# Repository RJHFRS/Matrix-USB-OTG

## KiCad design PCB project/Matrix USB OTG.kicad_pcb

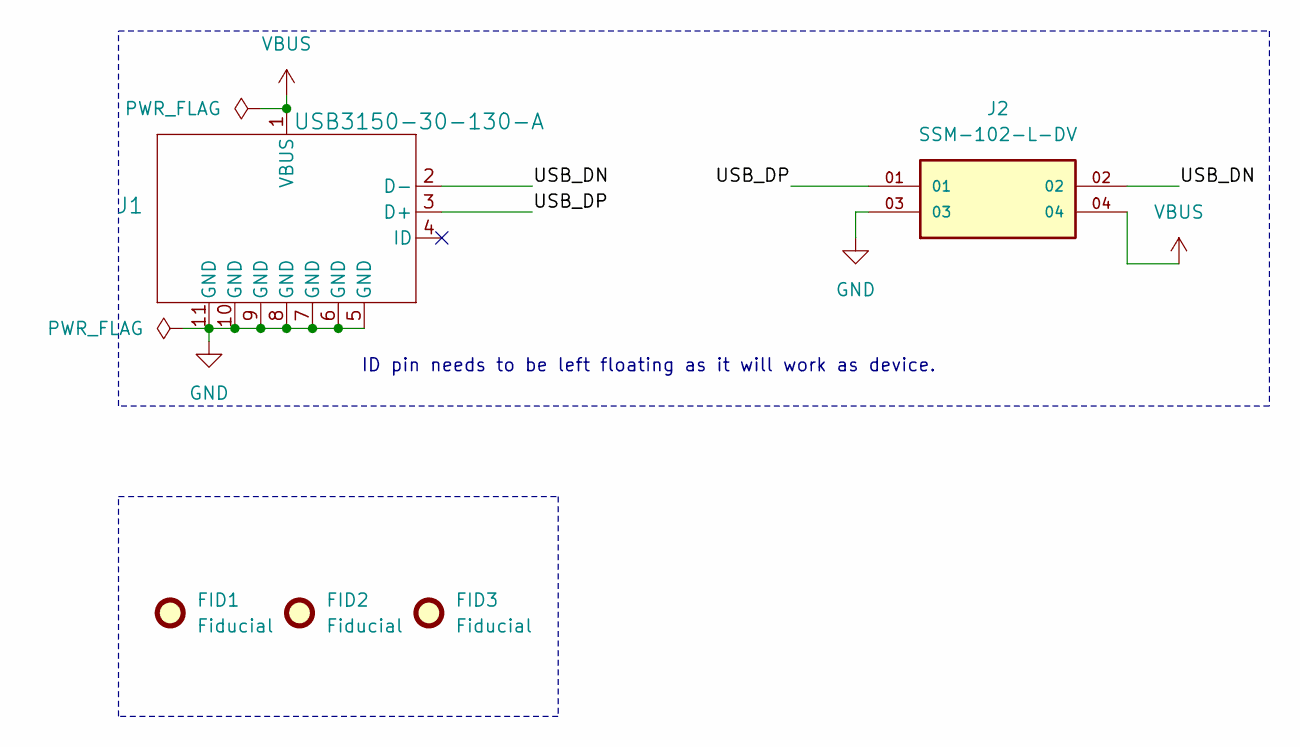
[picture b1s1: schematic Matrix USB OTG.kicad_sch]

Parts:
FID1, FID2, FID3: Fiducial; Fiducial_0.5mm_Mask1.5mm
J1: USB3150-30-130-A; USB3150-30-130-A_GCC; Digikey PN 2073-USB3150-30-130-ACT-ND - Cut Tape (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
J2: SSM-102-L-DV; SAMTEC_SSM-102-L-DV; PARTREV R; Digikey PN 612-SSM-102-L-DV-ND

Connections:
/USB_DN: J1.2 (D-), J2.02
/USB_DP: J1.3 (D+), J2.01
GND: J1.5 (GND), J1.6 (GND), J1.7 (GND), J1.8 (GND), J1.9 (GND), J1.10 (GND), J1.11 (GND), J2.03
VBUS: J1.1 (VBUS), J2.04

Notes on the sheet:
ID pin needs to be left floating as it will work as device.

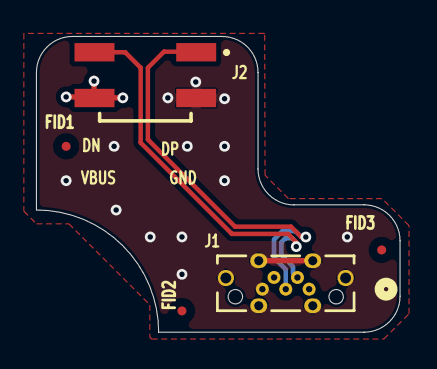
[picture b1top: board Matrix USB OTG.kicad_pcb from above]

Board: 4 copper layers, 20.2 x 16.4 mm, 5 parts (0 on the bottom side), 4 nets.
